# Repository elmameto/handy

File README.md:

# handy
An Arduino based pocket-sized bluetooth controller for your electric longboard (or else)

**_Will upload more information as soon as I can_**
Meanwhile, you can get more details from [https://hackaday.io/project/20748-electric-longboard-bluetooth-controller-handy](here)

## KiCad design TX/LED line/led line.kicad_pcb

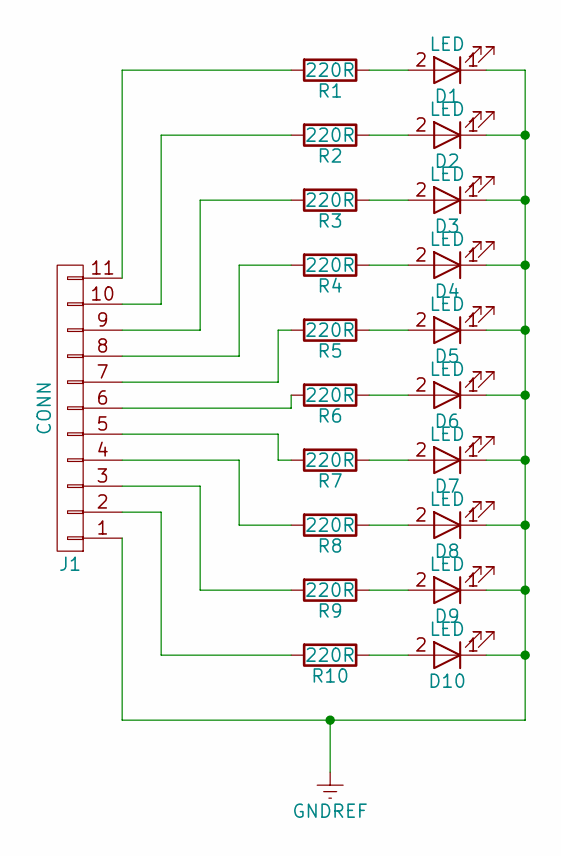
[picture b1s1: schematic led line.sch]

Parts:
D1, D2, D3, D4, D5, D6, D7, D8, D9, D10: LED; LED_3528
J1: CONN; Pin_Header_Straight_1x11
R1, R2, R3, R4, R5, R6, R7, R8, R9, R10: 220R; R_0603

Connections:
GNDREF: D1.1 (K), D2.1 (K), D3.1 (K), D4.1 (K), D5.1 (K), D6.1 (K), D7.1 (K), D8.1 (K), D9.1 (K), D10.1 (K), J1.1
unnamed: D1.2 (A), R1.1
unnamed: D2.2 (A), R2.1
unnamed: D3.2 (A), R3.1
unnamed: D4.2 (A), R4.1
unnamed: D5.2 (A), R5.1
unnamed: D6.2 (A), R6.1
unnamed: D7.2 (A), R7.1
unnamed: D8.2 (A), R8.1
unnamed: D9.2 (A), R9.1
unnamed: D10.2 (A), R10.1
unnamed: J1.2, R10.2
unnamed: J1.3, R9.2
unnamed: J1.4, R8.2
unnamed: J1.5, R7.2
unnamed: J1.6, R6.2
unnamed: J1.7, R5.2
unnamed: J1.8, R4.2
unnamed: J1.9, R3.2
unnamed: J1.10, R2.2
unnamed: J1.11, R1.2

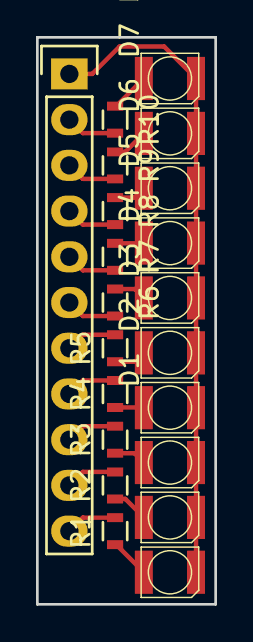
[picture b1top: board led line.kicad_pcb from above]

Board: 2 copper layers, 9.9 x 31.5 mm, 21 parts (0 on the bottom side), 21 nets.

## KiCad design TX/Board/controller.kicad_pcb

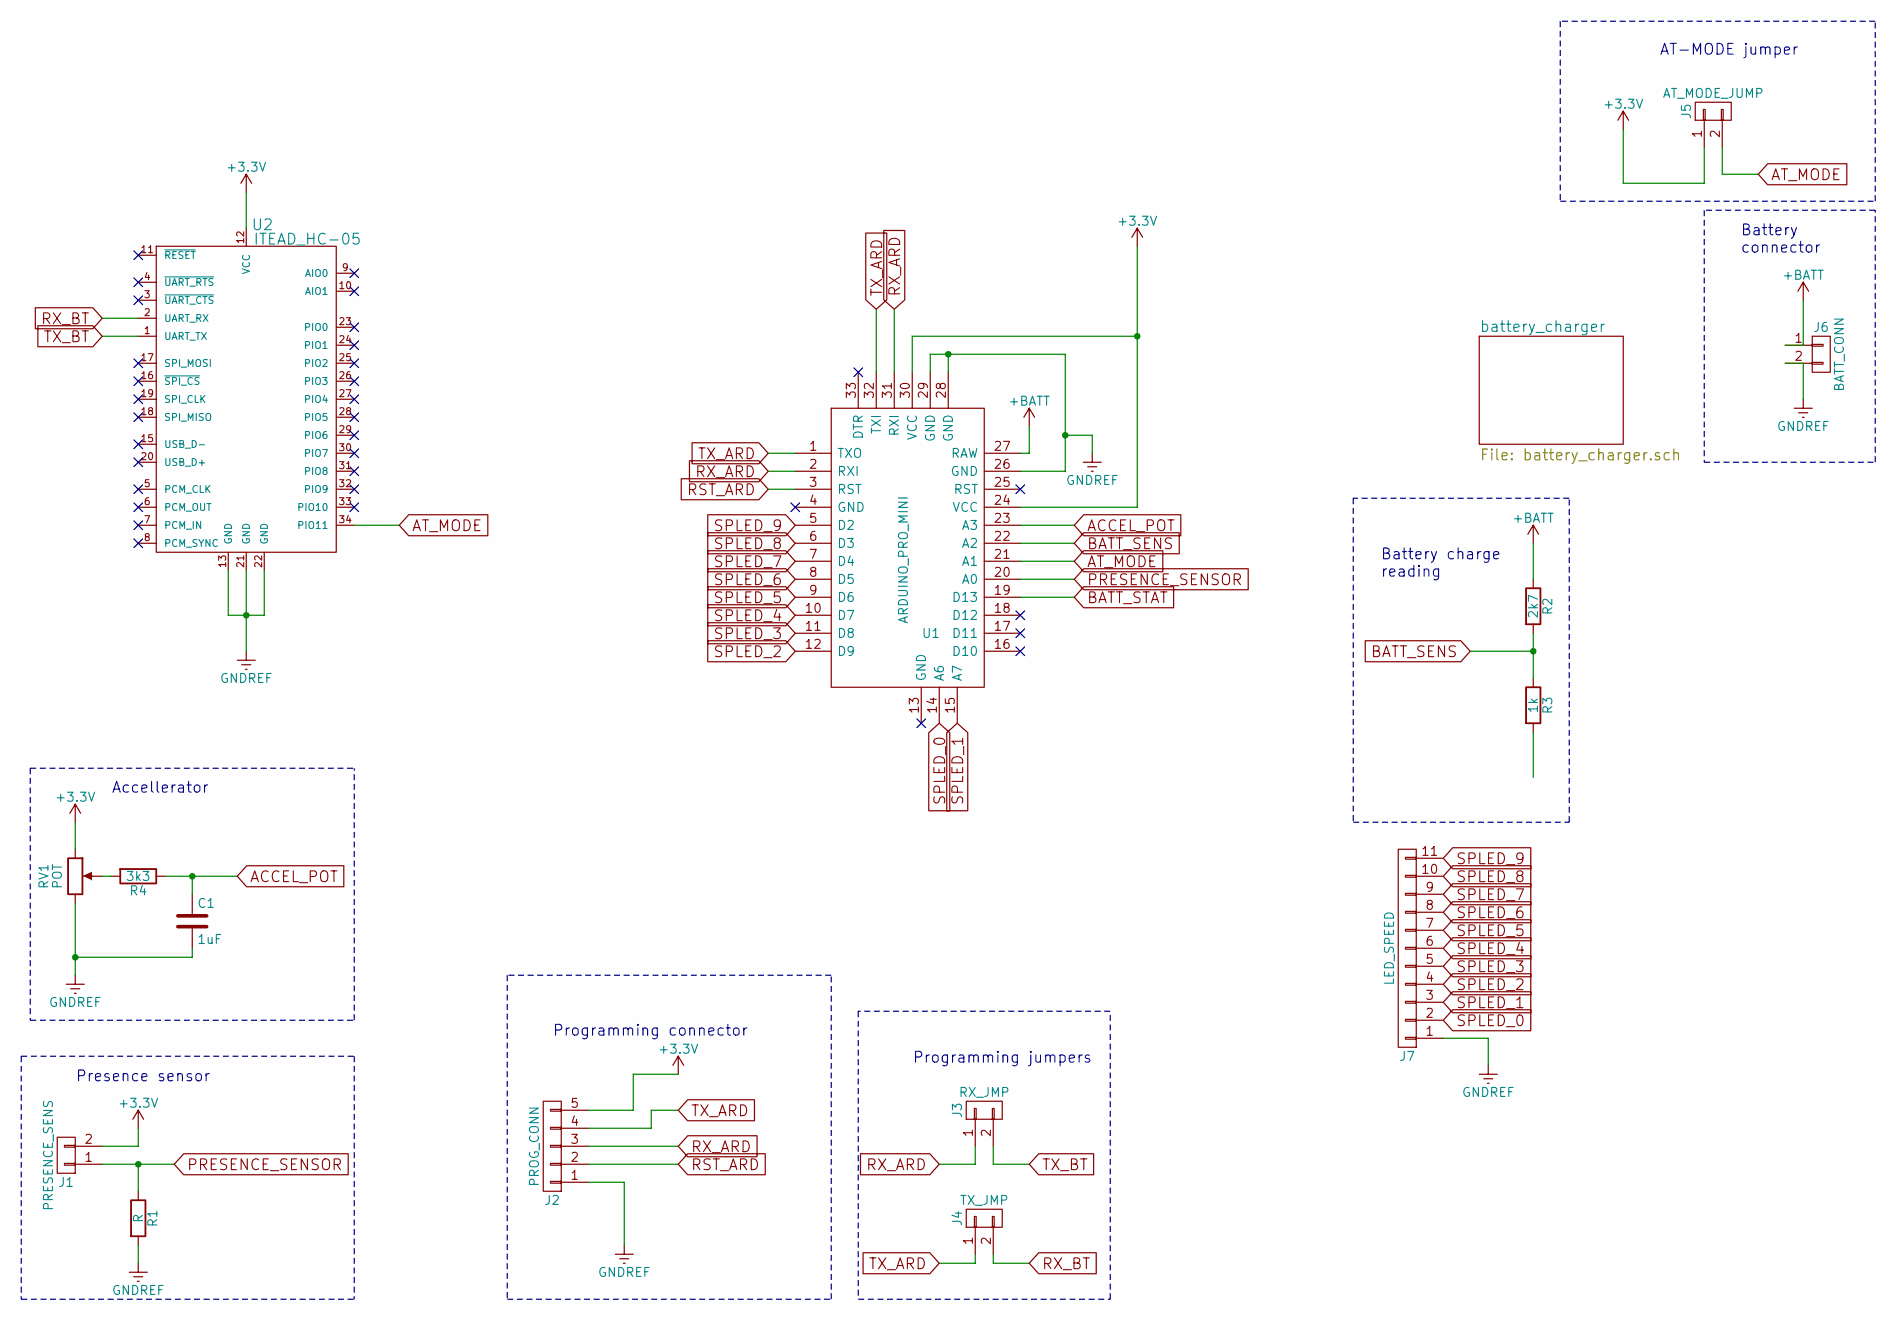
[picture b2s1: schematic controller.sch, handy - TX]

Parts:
C1: 1uF; C_Rect_L4_W2.5_P2.5
J1: PRESENCE_SENS; Pin_Header_Straight_1x02
J2: PROG_CONN; Pin_Header_Straight_1x05
J3: RX_JMP; Pin_Header_Straight_1x02
J4: TX_JMP; Pin_Header_Straight_1x02
J5: AT_MODE_JUMP; Pin_Header_Straight_1x02
J6: BATT_CONN; Pin_Header_Straight_1x02
J7: LED_SPEED; Pin_Header_Straight_1x11
R1: R; Resistor_Horizontal_RM7mm
R2: 2k7; Resistor_Horizontal_RM7mm
R3: 1k; Resistor_Horizontal_RM7mm
R4: 3k3; Resistor_Horizontal_RM7mm
RV1: POT; Potenziometro_PIHER_10mm_diametro
U1: ARDUINO_PRO_MINI; Arduino_PRO_MINI
U2: ITEAD_HC-05; HC-05

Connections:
+3V3: J1.2, J2.5, J5.1, RV1.1, U1.24 (VCC), U1.30 (VCC), U2.12 (VCC)
+BATT: J6.1, R2.1, U1.27 (RAW)
ACCEL_POT: C1.1, R4.1, U1.23 (A3)
AT_MODE: J5.2, U1.21 (A1), U2.34 (PIO11)
BATT_SENS: R2.2, R3.1, U1.22 (A2)
GNDREF: C1.2, J2.1, J6.2, J7.1, R1.2, RV1.3, U1.26 (GND), U1.28 (GND), U1.29 (GND), U2.13 (GND), U2.21 (GND), U2.22 (GND)
unnamed: R4.2, RV1.2
PRESENCE_SENSOR: J1.1, R1.1, U1.20 (A0)
RST_ARD: J2.2, U1.3 (RST)
RX_ARD: J2.3, J3.1, U1.2 (RXI), U1.31 (RXI)
RX_BT: J4.2, U2.2 (UART_RX)
SPLED_0: J7.2, U1.14 (A6)
SPLED_1: J7.3, U1.15 (A7)
SPLED_2: J7.4, U1.12 (D9)
SPLED_3: J7.5, U1.11 (D8)
SPLED_4: J7.6, U1.10 (D7)
SPLED_5: J7.7, U1.9 (D6)
SPLED_6: J7.8, U1.8 (D5)
SPLED_7: J7.9, U1.7 (D4)
SPLED_8: J7.10, U1.6 (D3)
SPLED_9: J7.11, U1.5 (D2)
TX_ARD: J2.4, J4.1, U1.1 (TXO), U1.32 (TXI)
TX_BT: J3.2, U2.1 (UART_TX)

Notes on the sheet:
Accellerator
Programming jumpers
Programming connector
Presence sensor
AT-MODE jumper
Battery connector
Battery charge reading

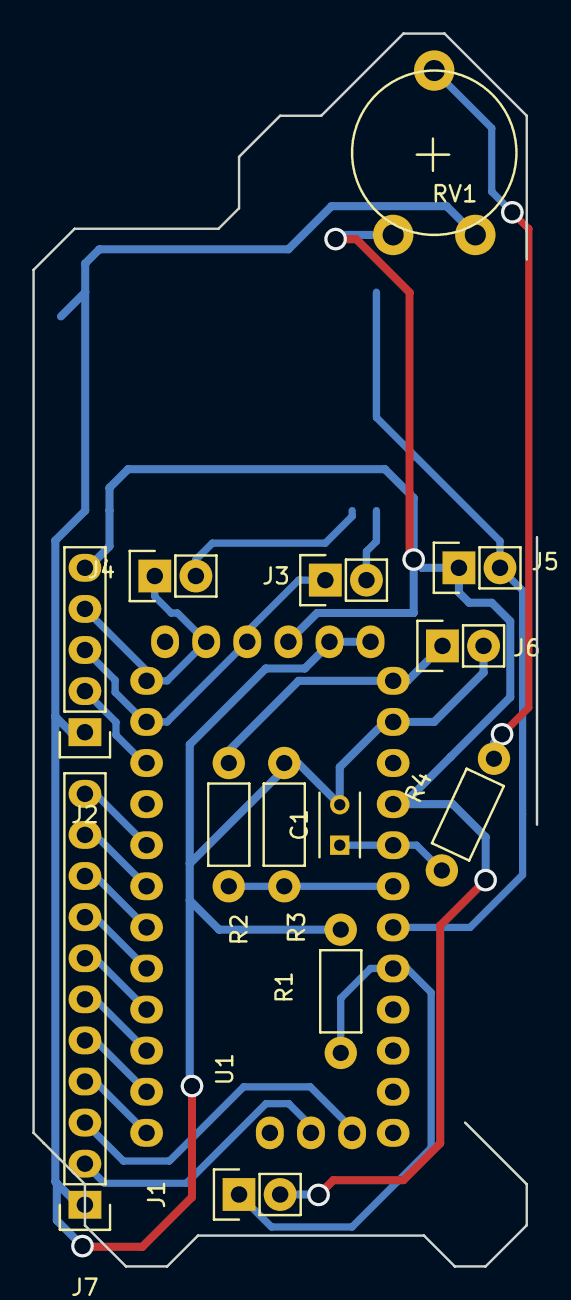
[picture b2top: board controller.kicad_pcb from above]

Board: 2 copper layers, 31.1 x 76.2 mm, 15 parts (1 on the bottom side), 23 nets.

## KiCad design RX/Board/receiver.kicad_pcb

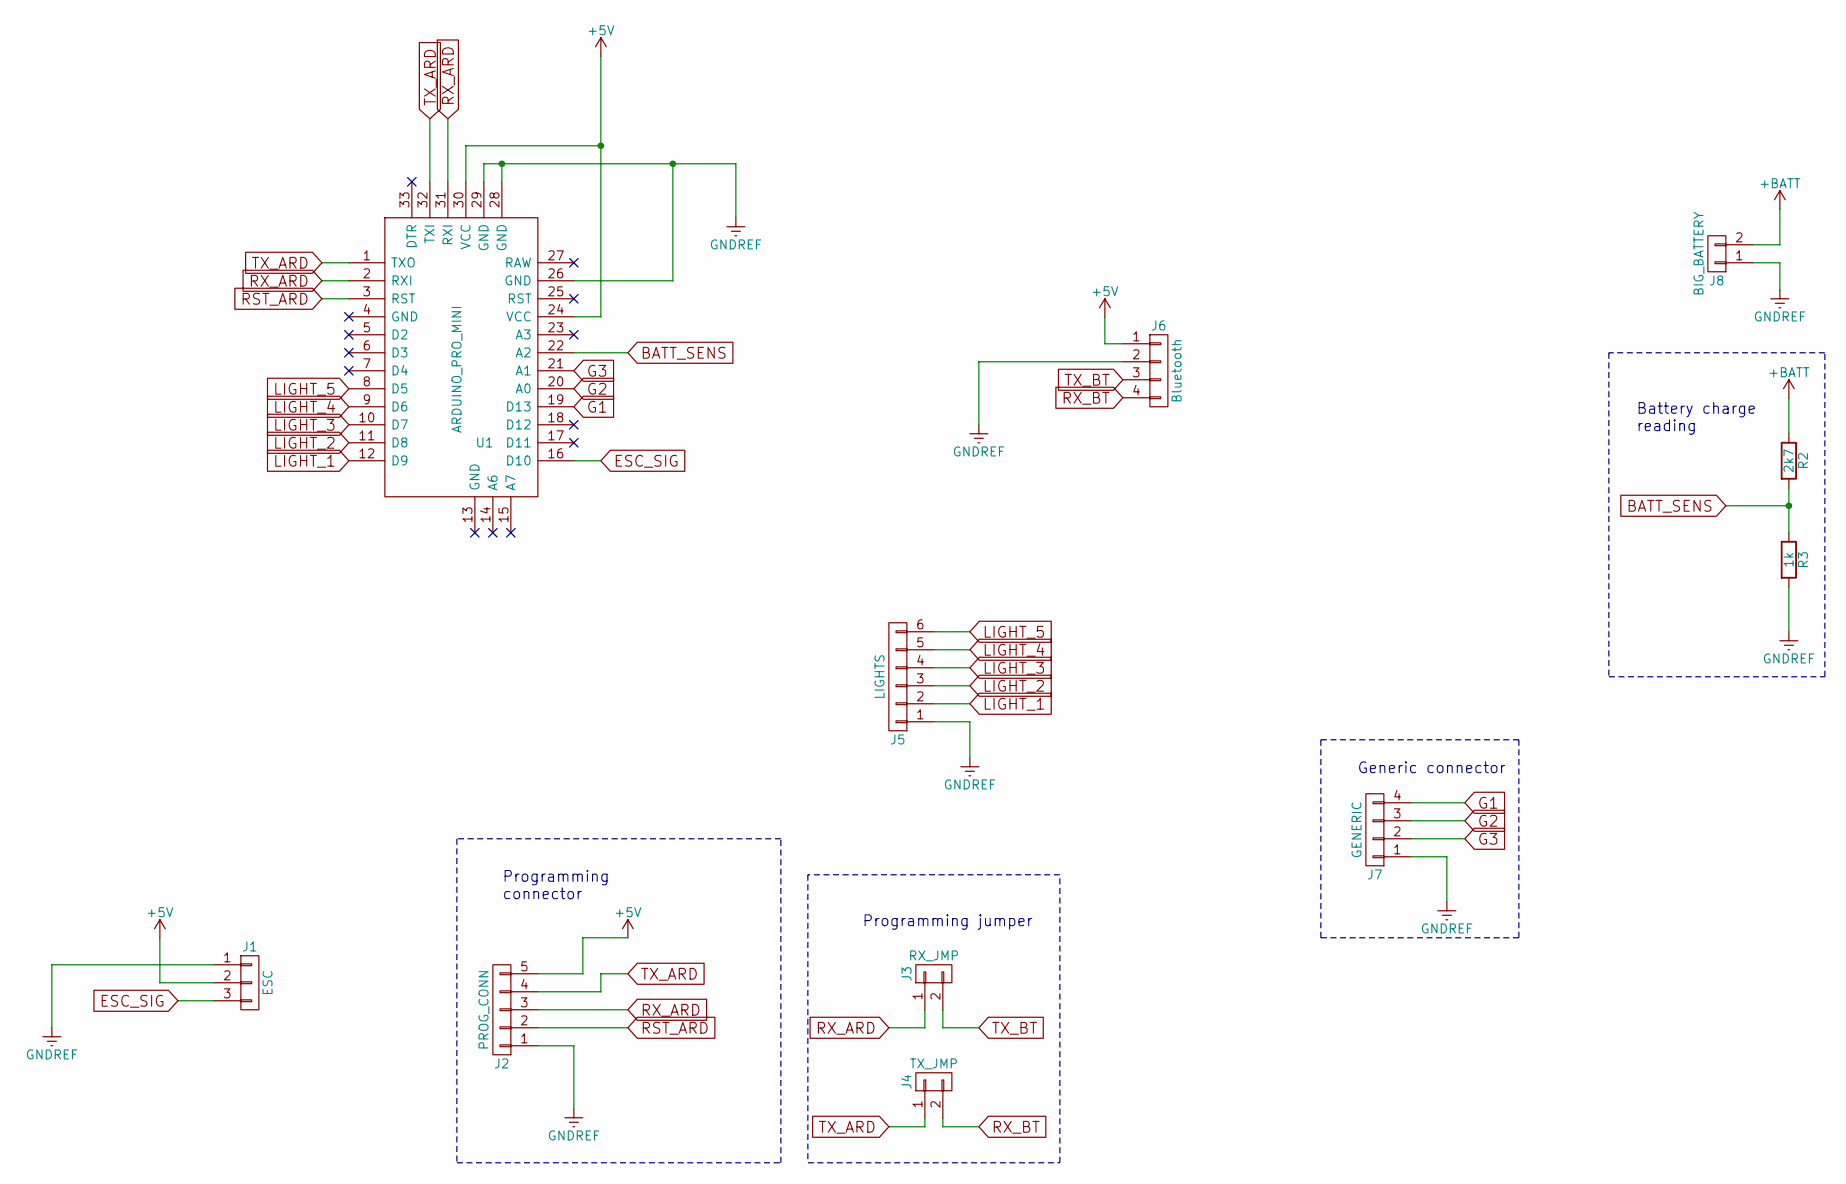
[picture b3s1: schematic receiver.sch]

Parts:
J1: ESC; Pin_Header_Angled_1x03
J2: PROG_CONN; Pin_Header_Straight_1x05
J3: RX_JMP; Pin_Header_Straight_1x02
J4: TX_JMP; Pin_Header_Straight_1x02
J5: LIGHTS; Pin_Header_Angled_1x06
J6: Bluetooth; Pin_Header_Angled_1x04
J7: GENERIC; Pin_Header_Angled_1x04
J8: BIG_BATTERY; Pin_Header_Angled_1x02
R2: 2k7; Resistor_Horizontal_RM7mm
R3: 1k; Resistor_Horizontal_RM7mm
U1: ARDUINO_PRO_MINI; Arduino_PRO_MINI

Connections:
+5V: J1.2, J2.5, J6.1, U1.24 (VCC), U1.30 (VCC)
+BATT: J8.2, R2.1
BATT_SENS: R2.2, R3.1, U1.22 (A2)
ESC_SIG: J1.3, U1.16 (D10)
G1: J7.4, U1.19 (D13)
G2: J7.3, U1.20 (A0)
G3: J7.2, U1.21 (A1)
GNDREF: J1.1, J2.1, J5.1, J6.2, J7.1, J8.1, R3.2, U1.26 (GND), U1.28 (GND), U1.29 (GND)
LIGHT_1: J5.2, U1.12 (D9)
LIGHT_2: J5.3, U1.11 (D8)
LIGHT_3: J5.4, U1.10 (D7)
LIGHT_4: J5.5, U1.9 (D6)
LIGHT_5: J5.6, U1.8 (D5)
RST_ARD: J2.2, U1.3 (RST)
RX_ARD: J2.3, J3.1, U1.2 (RXI), U1.31 (RXI)
RX_BT: J4.2, J6.4
TX_ARD: J2.4, J4.1, U1.1 (TXO), U1.32 (TXI)
TX_BT: J3.2, J6.3

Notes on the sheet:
Programming jumper
Programming connector
Battery charge reading
Generic connector

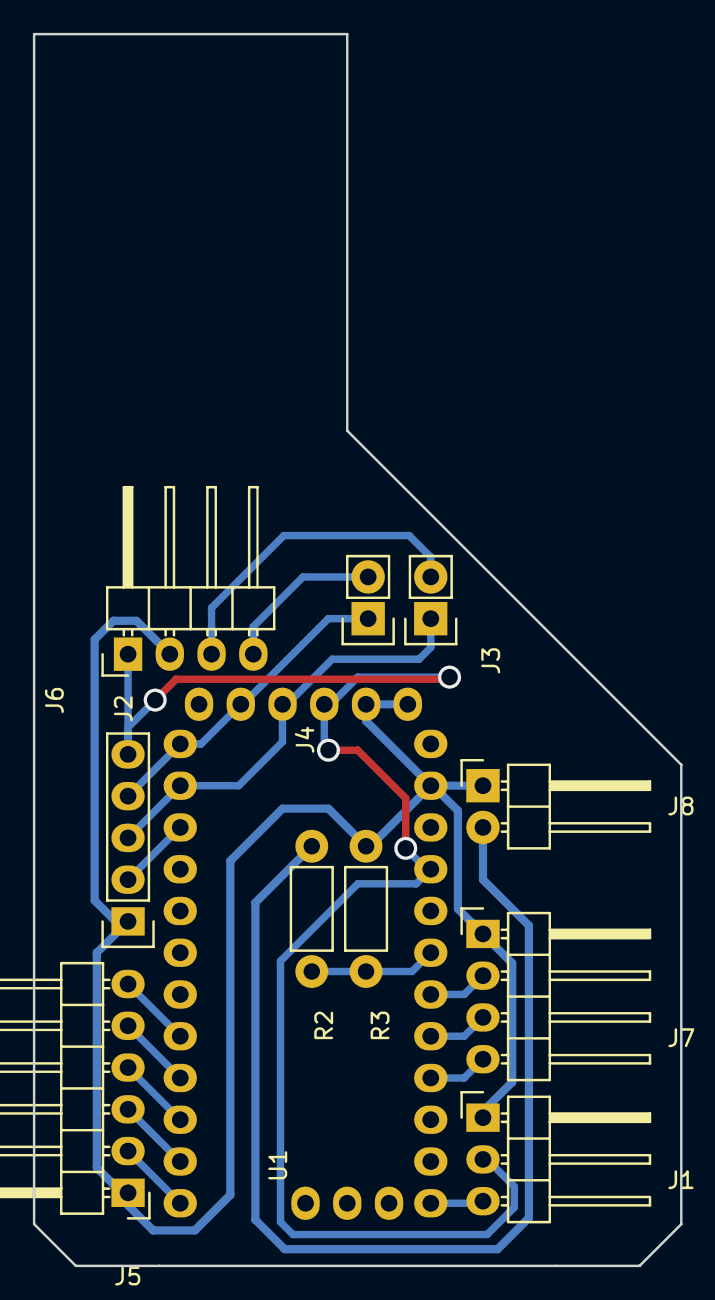
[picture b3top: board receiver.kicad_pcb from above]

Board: 2 copper layers, 39.4 x 74.9 mm, 11 parts (0 on the bottom side), 18 nets.

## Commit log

2017-04-02 Corrected bugs and added first prototype of receiver board
2017-04-04 Added low-pass filter to the transmitter -> stable acc reading
2017-04-04 First working version of the receiver board
2017-04-06 Added images and first version of the led panel
